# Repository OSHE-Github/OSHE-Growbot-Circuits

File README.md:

# OSHE-Growbot-Circuits
 Directory for all of the circuits created for the Growbot

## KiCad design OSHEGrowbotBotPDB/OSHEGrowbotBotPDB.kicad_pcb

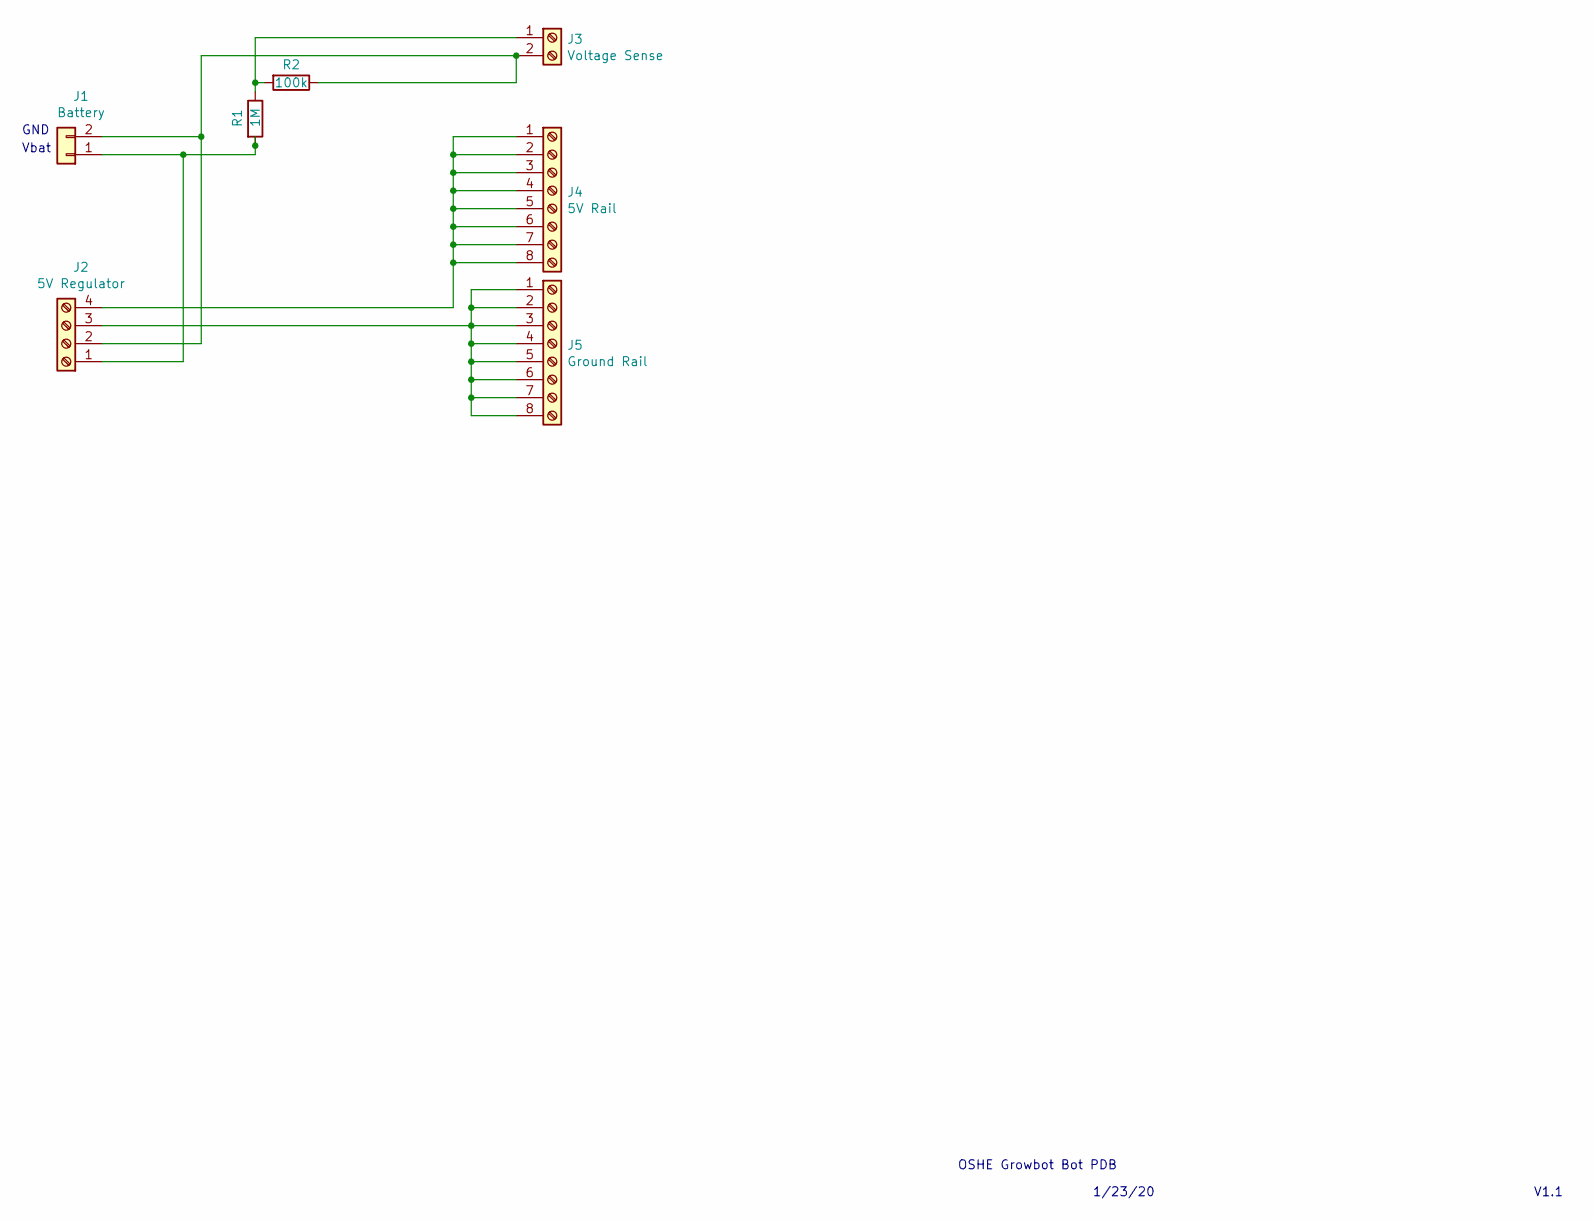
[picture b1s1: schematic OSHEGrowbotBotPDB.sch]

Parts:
J1: Battery; pxc_1984963_04_PTSA-1-5-2-3-5-F
J2: 5V Regulator; pxc_1935792_01_PT-2-5-4-5-0-H
J3: Voltage Sense; pxc_1984963_04_PTSA-1-5-2-3-5-F
J4: 5V Rail; pxc_1985027_04_PTSA-1-5-8-3-5-F
J5: Ground Rail; pxc_1985027_04_PTSA-1-5-8-3-5-F
R1: 1M; R_Axial_DIN0207_L6.3mm_D2.5mm_P7.62mm_Horizontal
R2: 100k; R_Axial_DIN0207_L6.3mm_D2.5mm_P7.62mm_Horizontal

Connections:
unnamed: J1.1, J2.1, R1.2
unnamed: J1.2, J2.2, J3.2, R2.1
unnamed: J2.3, J5.1, J5.2, J5.3, J5.4, J5.5, J5.6, J5.7, J5.8
unnamed: J2.4, J4.1, J4.2, J4.3, J4.4, J4.5, J4.6, J4.7, J4.8
unnamed: J3.1, R1.1, R2.2

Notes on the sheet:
GND
Vbat
OSHE Growbot Bot PDB
1/23/20
V1.1

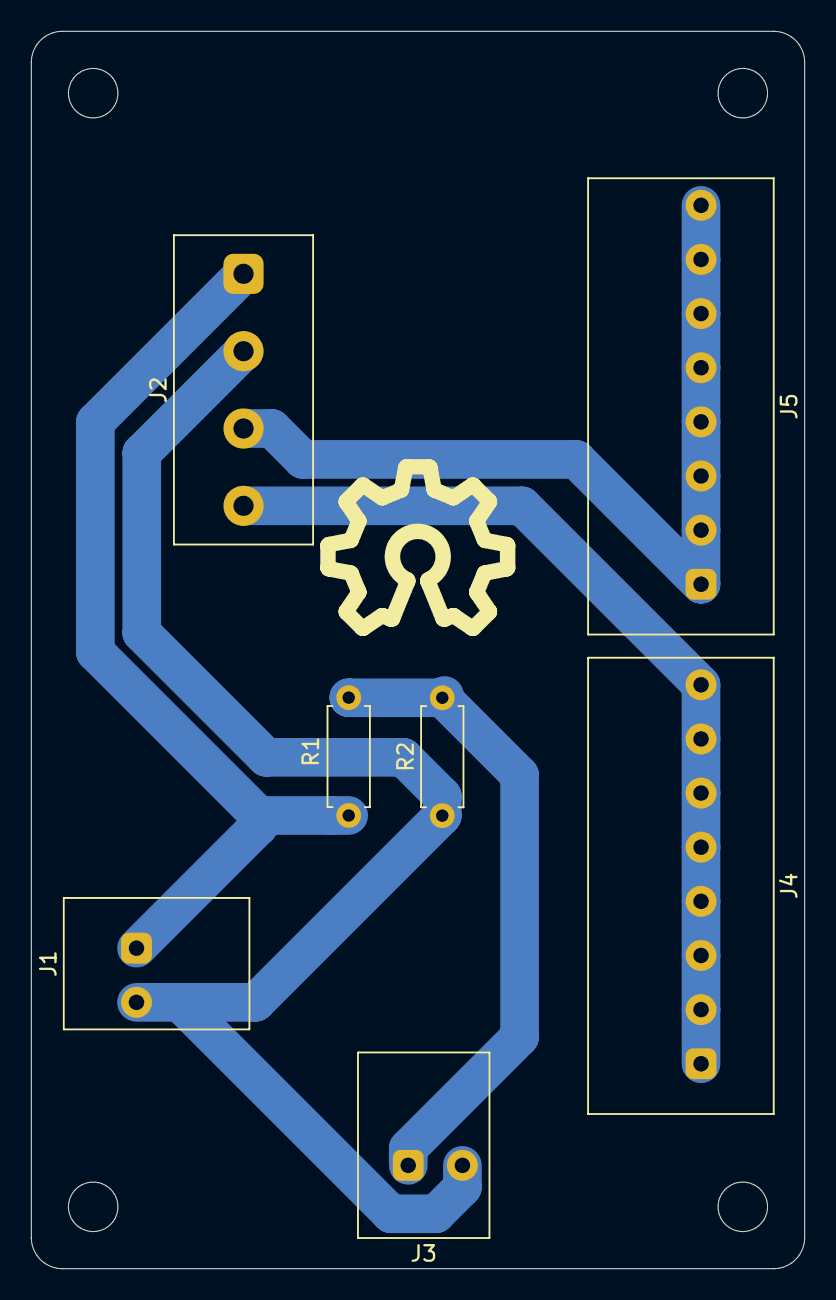
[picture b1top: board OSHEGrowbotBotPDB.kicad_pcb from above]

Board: 2 copper layers, 50.0 x 80.0 mm, 7 parts (0 on the bottom side), 5 nets.

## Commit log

2020-01-22 Created rough schematic
2020-01-26 PDB with Battery Connection
2020-01-27 Final draft, time for verification
